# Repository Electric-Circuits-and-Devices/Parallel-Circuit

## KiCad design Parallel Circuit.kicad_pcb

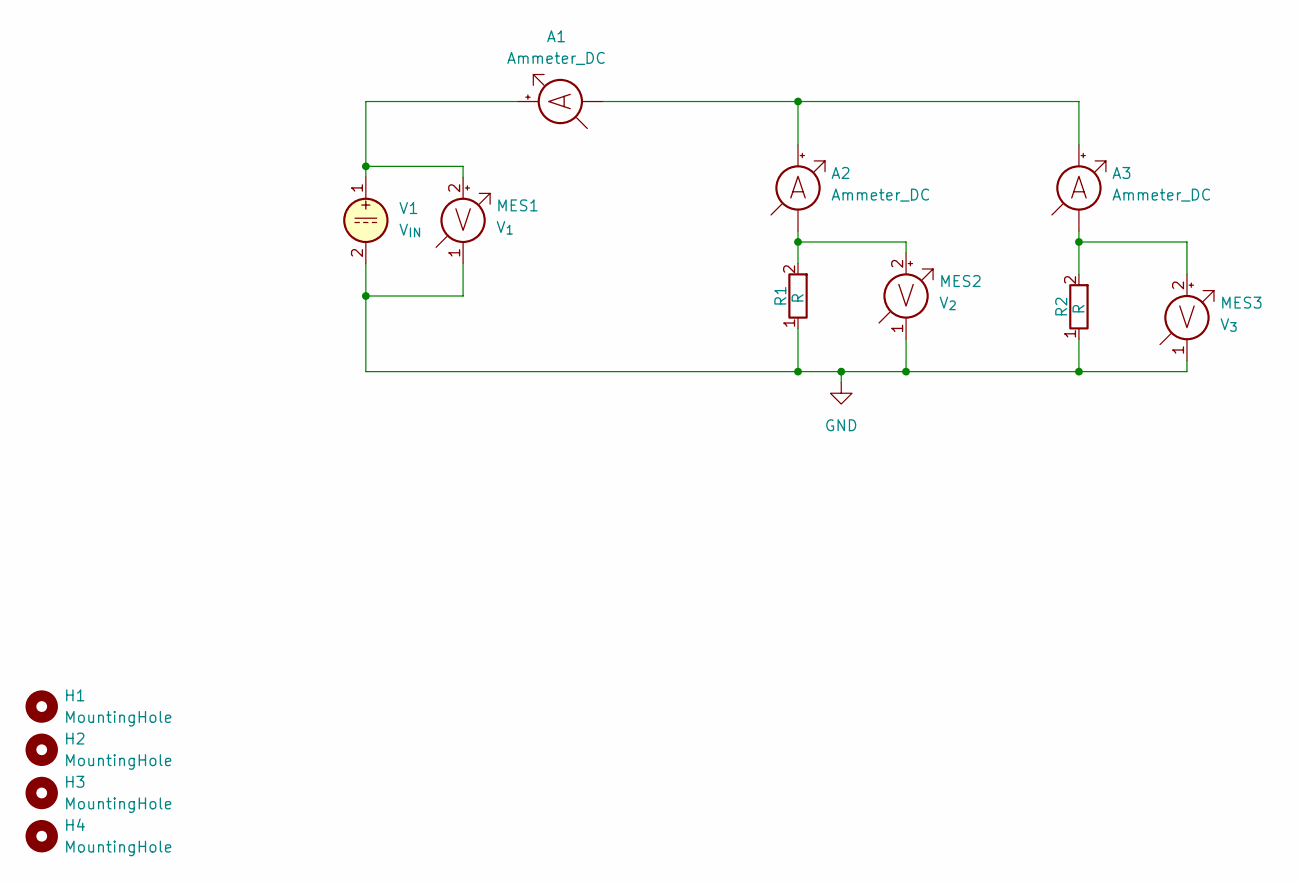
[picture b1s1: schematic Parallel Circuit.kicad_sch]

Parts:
A1: Ammeter_DC; Ammeter horizontal
A2, A3: Ammeter_DC; Ammeter Vertical
H1, H2, H3, H4: MountingHole; MountingHole_3.2mm_M3_Pad
MES1: V_{1}; Volt meter vertical
MES2: V_{2}; Volt meter vertical
MES3: V_{3}; Volt meter vertical
R1, R2: R; Resistor-Plugin_0.5Watt
V1: V_{IN}; DC Power Supply Vertical

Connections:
GND: MES1.1 (-), MES2.1 (-), MES3.1 (-), R1.1, R2.1, V1.2
unnamed: A1.2 (+), MES1.2 (+), V1.1
unnamed: A1.1 (-), A2.2 (+), A3.2 (+)
unnamed: A2.1 (-), MES2.2 (+), R1.2
unnamed: A3.1 (-), MES3.2 (+), R2.2

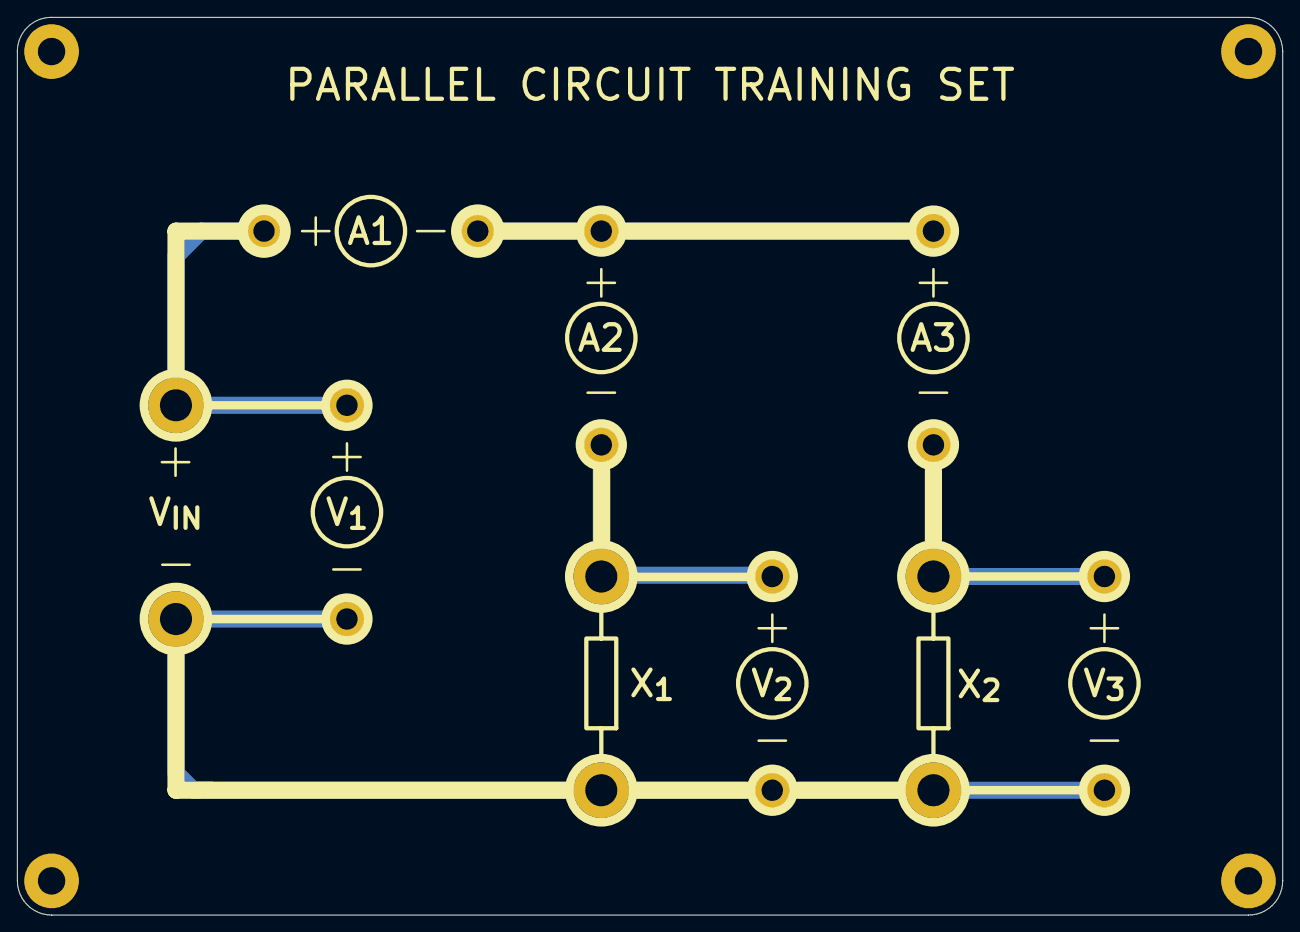
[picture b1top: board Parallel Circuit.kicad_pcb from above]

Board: 2 copper layers, 148.0 x 105.0 mm, 13 parts (0 on the bottom side), 5 nets.
